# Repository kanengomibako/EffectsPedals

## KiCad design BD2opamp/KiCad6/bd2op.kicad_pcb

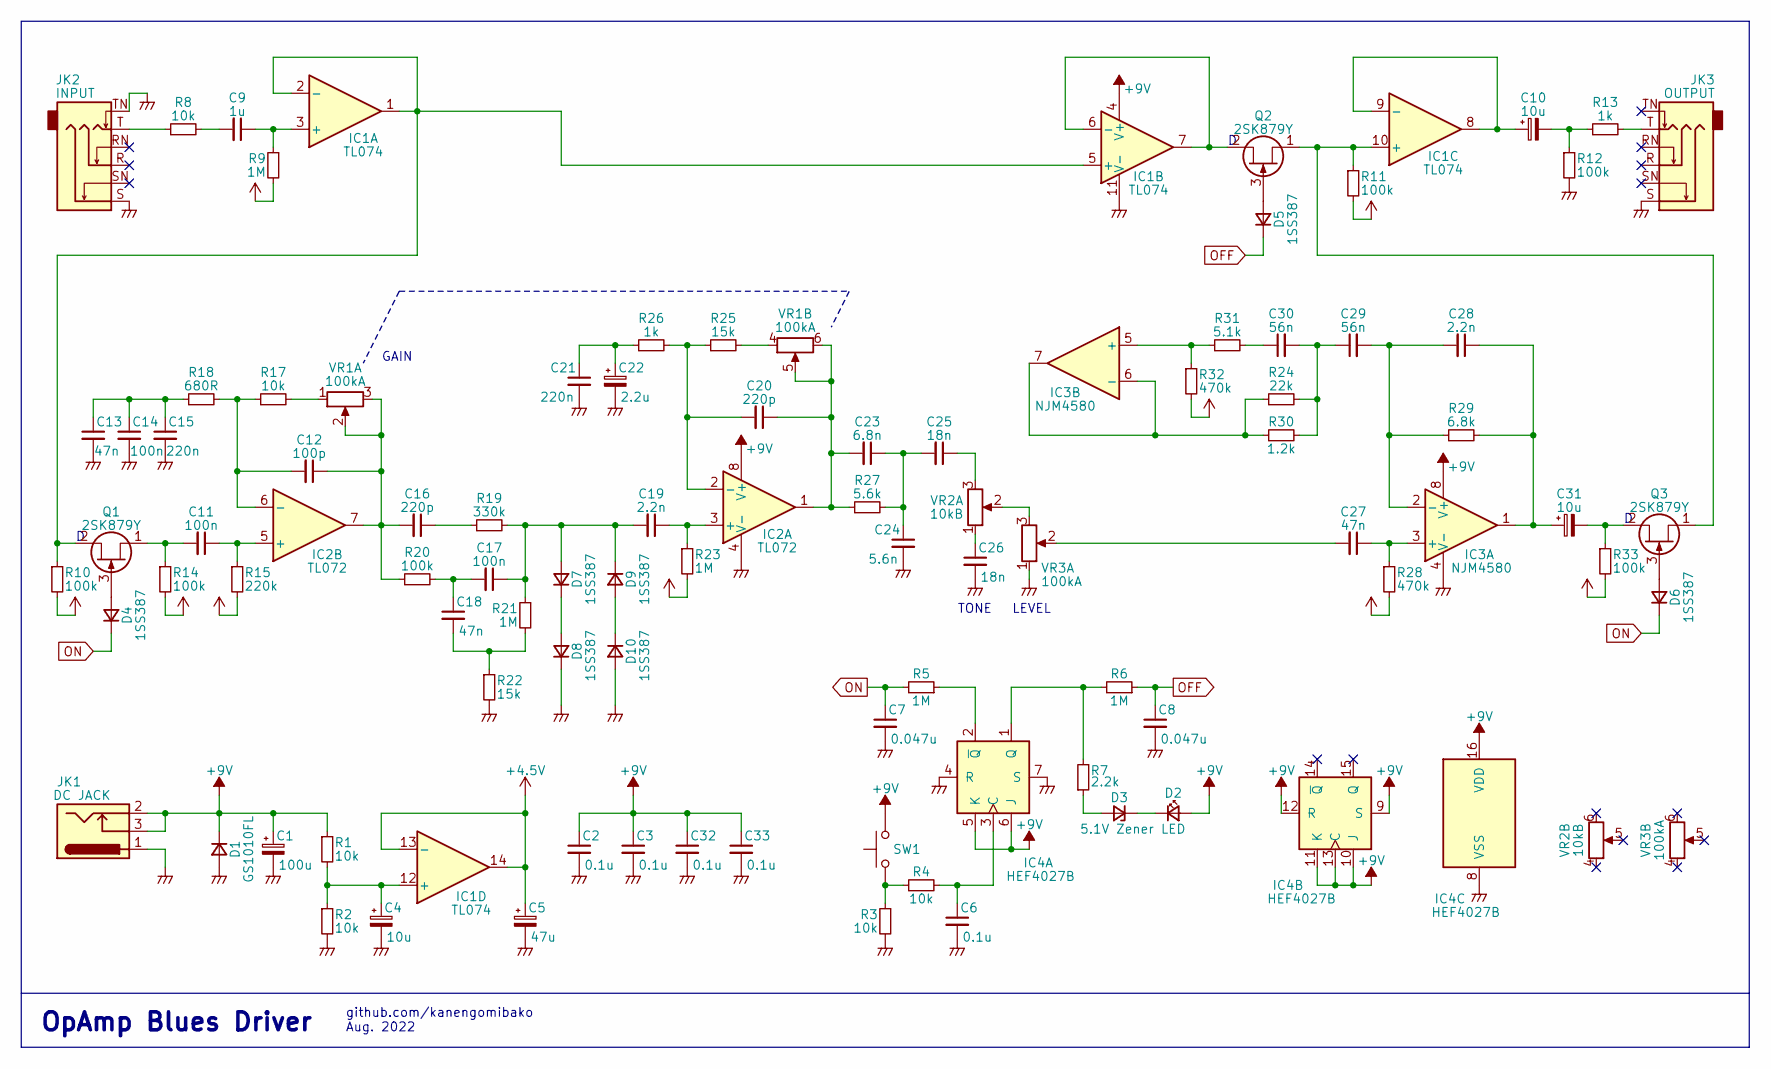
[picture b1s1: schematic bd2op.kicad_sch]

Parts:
C1: 100u; CP_Elec_6.3x5.4_Nichicon
C2, C3, C6, C32, C33: 0.1u; C_0603_1608Metric_Pad1.08x0.95mm_HandSolder
C4, C10, C31: 10u; CP_Elec_4x5.4
C5: 47u; CP_Elec_5x5.4
C7, C8: 0.047u; C_0603_1608Metric_Pad1.08x0.95mm_HandSolder
C9: 1u; C_1206_3216Metric
C11, C17: 100n; C_1206_3216Metric
C12: 100p; C_0603_1608Metric_Pad1.08x0.95mm_HandSolder
C13: 47n; C_1210_3225Metric
C14: 100n; C_1210_3225Metric
C15, C21: 220n; C_1210_3225Metric
C16, C20: 220p; C_0603_1608Metric_Pad1.08x0.95mm_HandSolder
C18, C27: 47n; C_1206_3216Metric
C19, C28: 2.2n; C_0603_1608Metric_Pad1.08x0.95mm_HandSolder
C22: 2.2u; CP_Elec_4x5.4
C23: 6.8n; C_0603_1608Metric_Pad1.08x0.95mm_HandSolder
C24: 5.6n; C_0603_1608Metric_Pad1.08x0.95mm_HandSolder
C25, C26: 18n; C_0805_2012Metric
C29, C30: 56n; C_1206_3216Metric
D1: GS1010FL; my_D_GS1010FL
D2: LED; my_LED_3mm
D3: 5.1V Zener; my_D_SOD-123
D4, D5, D6, D7, D8, D9, D10: 1SS387; D_SOD-523_HandSoldering
IC1: TL074; my_TSSOP-14
IC2: TL072; DIP-8_W7.62mm
IC3: NJM4580; my_SOIC-8_3.9x4.9mm_Pitch1.27mm
IC4: HEF4027B; my_SOIC-16_3.9x9.9mm_Pitch1.27mm
JK1: DC JACK; my_DC_Jack
JK2: INPUT; my_Phone_Jack_Daier
JK3: OUTPUT; my_Phone_Jack_Daier
Q1, Q2, Q3: 2SK879Y; SOT-323_SC-70_Handsoldering
R1, R2, R3, R4, R8, R17: 10k; R_0603_1608Metric_Pad0.98x0.95mm_HandSolder
R5, R6, R9, R21, R23: 1M; R_0603_1608Metric_Pad0.98x0.95mm_HandSolder
R7: 2.2k; R_0603_1608Metric_Pad0.98x0.95mm_HandSolder
R10, R11, R12, R14, R20, R33: 100k; R_0603_1608Metric_Pad0.98x0.95mm_HandSolder
R13, R26: 1k; R_0805_2012Metric
R15: 220k; R_0603_1608Metric_Pad0.98x0.95mm_HandSolder
R18: 680R; R_0805_2012Metric
R19: 330k; R_0603_1608Metric_Pad0.98x0.95mm_HandSolder
R22, R25: 15k; R_0603_1608Metric_Pad0.98x0.95mm_HandSolder
R24: 22k; R_0603_1608Metric_Pad0.98x0.95mm_HandSolder
R27: 5.6k; R_0603_1608Metric_Pad0.98x0.95mm_HandSolder
R28, R32: 470k; R_0603_1608Metric_Pad0.98x0.95mm_HandSolder
R29: 6.8k; R_0603_1608Metric_Pad0.98x0.95mm_HandSolder
R30: 1.2k; R_0603_1608Metric_Pad0.98x0.95mm_HandSolder
R31: 5.1k; R_0603_1608Metric_Pad0.98x0.95mm_HandSolder
SW1: SW_Push; my_SKHCBFA010
VR1, VR3: 100kA; my_pot_slide_20mm_travel
VR2: 10kB; my_pot_slide_20mm_travel

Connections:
+4.5V: C5.1, IC1.13 (-), IC1.14, R9.2, R10.2, R11.2, R14.2, R15.2, R23.2, R28.2, R32.2, R33.2
+9V: C1.1, C2.1, C3.1, C32.1, C33.1, D1.1 (K), D2.2 (A), IC1.4 (V+), IC2.8 (V+), IC3.8 (V+), IC4.5 (K), IC4.6 (J), IC4.9 (S), IC4.10 (J), IC4.11 (K), IC4.12 (R), IC4.13 (C), IC4.16 (VDD), JK1.2, JK1.3, R1.1, SW1.2
GND: C1.2, C2.2, C3.2, C4.2, C5.2, C6.2, C7.2, C8.2, C13.2, C14.2, C15.2, C21.2, C22.2, C24.2, C26.2, C32.2, C33.2, D1.2 (A), D8.1 (K), D10.2 (A), IC1.11 (V-), IC2.4 (V-), IC3.4 (V-), IC4.4 (R), IC4.7 (S), IC4.8 (VSS), JK1.1, JK2.S, JK2.TN, JK3.S, R2.2, R3.2, R12.2, R22.2, VR3.1
unnamed: C4.1, IC1.12 (+), R1.2, R2.1
unnamed: C6.1, IC4.3 (C), R4.2
unnamed: C9.1, IC1.3 (+), R9.1
unnamed: C9.2, R8.2
unnamed: C10.1, IC1.8, IC1.9 (-)
unnamed: C10.2, R12.1, R13.1
unnamed: C11.1, IC2.5 (+), R15.1
unnamed: C11.2, Q1.1 (S), R14.1
unnamed: C12.1, C16.2, IC2.7, R20.1, VR1.2, VR1.3
unnamed: C12.2, IC2.6 (-), R17.1, R18.2
unnamed: C13.1, C14.1, C15.1, R18.1
unnamed: C16.1, R19.1
unnamed: C17.1, C19.2, D7.2 (A), D9.1 (K), R19.2, R21.1
unnamed: C17.2, C18.1, R20.2
unnamed: C18.2, R21.2, R22.1
unnamed: C19.1, IC2.3 (+), R23.1
unnamed: C20.1, C23.2, IC2.1, R27.1, VR1.5, VR1.6
unnamed: C20.2, IC2.2 (-), R25.1, R26.2
unnamed: C21.1, C22.1, R26.1
unnamed: C23.1, C24.1, C25.2, R27.2
unnamed: C25.1, VR2.3
unnamed: C26.1, VR2.1
unnamed: C27.1, IC3.3 (+), R28.1
unnamed: C27.2, VR3.2
unnamed: C28.1, C31.1, IC3.1, R29.2
unnamed: C28.2, C29.2, IC3.2 (-), R29.1
unnamed: C29.1, C30.2, R24.2, R30.2
unnamed: C30.1, R31.2
unnamed: C31.2, Q3.2 (D), R33.1
unnamed: D2.1 (K), D3.1 (K)
unnamed: D3.2 (A), R7.1
unnamed: D4.2 (A), Q1.3 (G)
unnamed: D5.2 (A), Q2.3 (G)
unnamed: D6.2 (A), Q3.3 (G)
unnamed: D7.1 (K), D8.2 (A)
unnamed: D9.2 (A), D10.1 (K)
unnamed: IC1.1, IC1.2 (-), IC1.5 (+), Q1.2 (D), R10.1
unnamed: IC1.6 (-), IC1.7, Q2.2 (D)
unnamed: IC1.10 (+), Q2.1 (S), Q3.1 (S), R11.1
unnamed: IC3.5 (+), R31.1, R32.1
unnamed: IC3.6 (-), IC3.7, R24.1, R30.1
unnamed: IC4.1 (Q), R6.2, R7.2
unnamed: IC4.2 (~Q), R5.1
unnamed: JK2.T, R8.1
unnamed: JK3.T, R13.2
unnamed: R3.1, R4.1, SW1.1
unnamed: R17.2, VR1.1
unnamed: R25.2, VR1.4
unnamed: VR2.2, VR3.3
OFF: C8.1, D5.1 (K), R6.1
ON: C7.1, D4.1 (K), D6.1 (K), R5.2

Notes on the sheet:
OpAmp Blues Driver
GAIN
github.com/kanengomibako Aug. 2022
TONE LEVEL

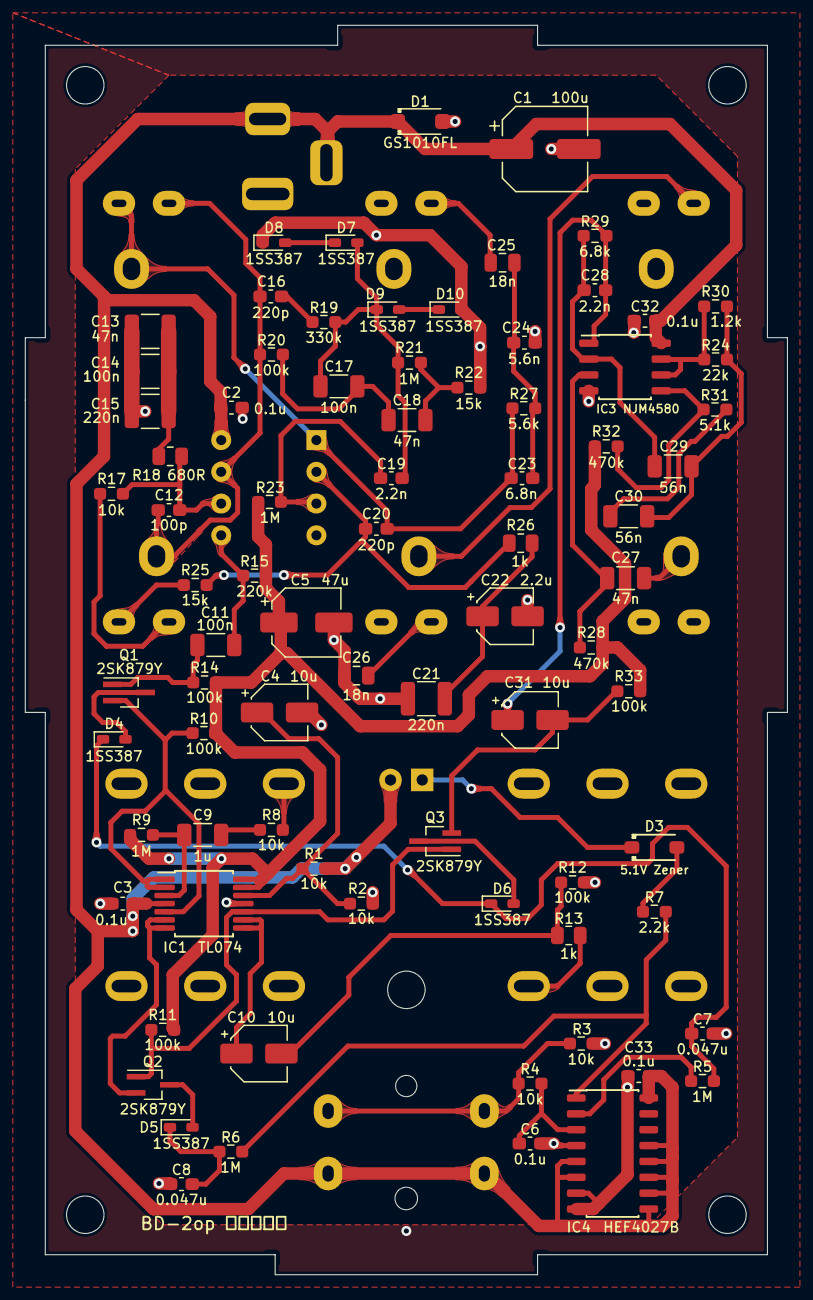
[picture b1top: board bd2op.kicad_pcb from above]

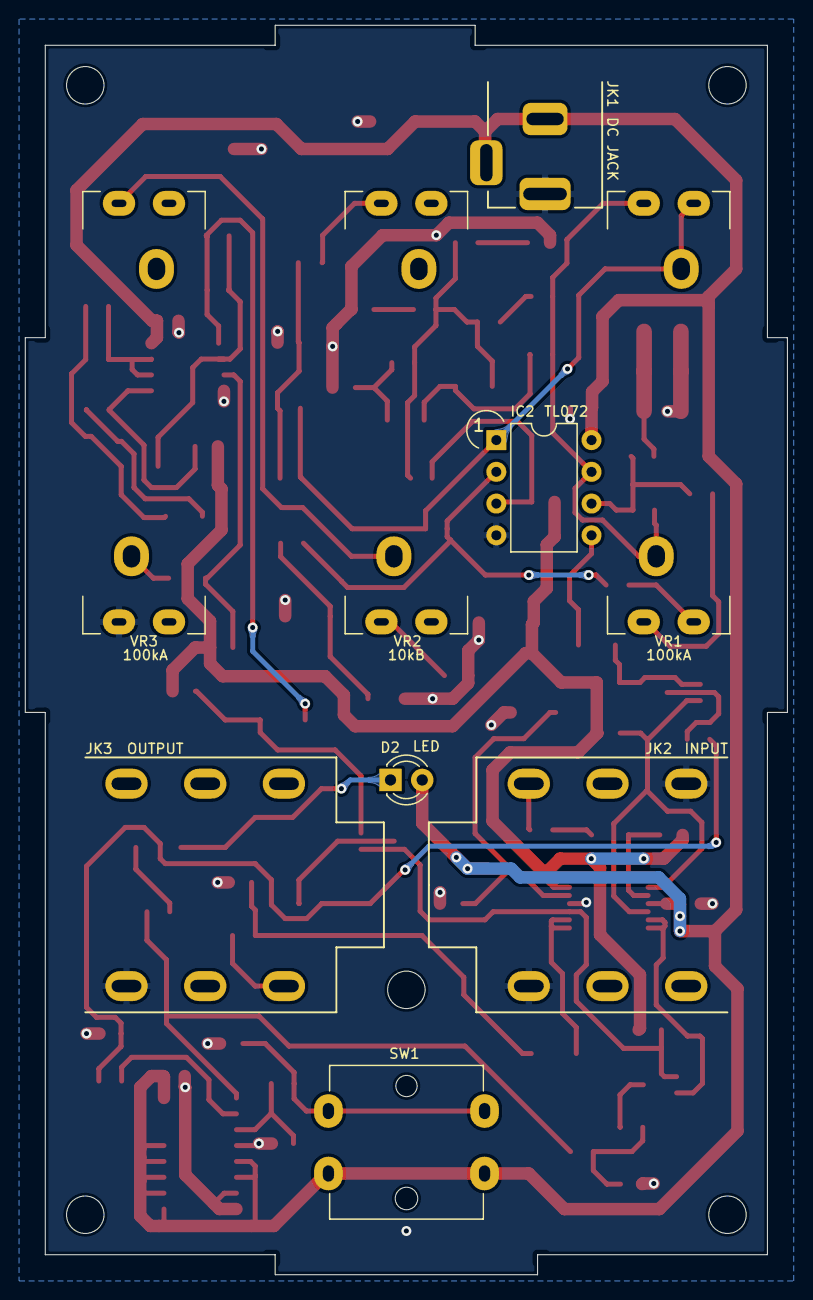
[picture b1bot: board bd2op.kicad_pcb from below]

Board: 2 copper layers, 61.0 x 100.0 mm, 102 parts (9 on the bottom side), 54 nets.

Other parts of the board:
r: h; kado
r#2, r#5, r#7, r#8, r#9, r#11, r#13: h; kado
r#3, r#4, r#6, r#10, r#12: h; Hole_0.4mm

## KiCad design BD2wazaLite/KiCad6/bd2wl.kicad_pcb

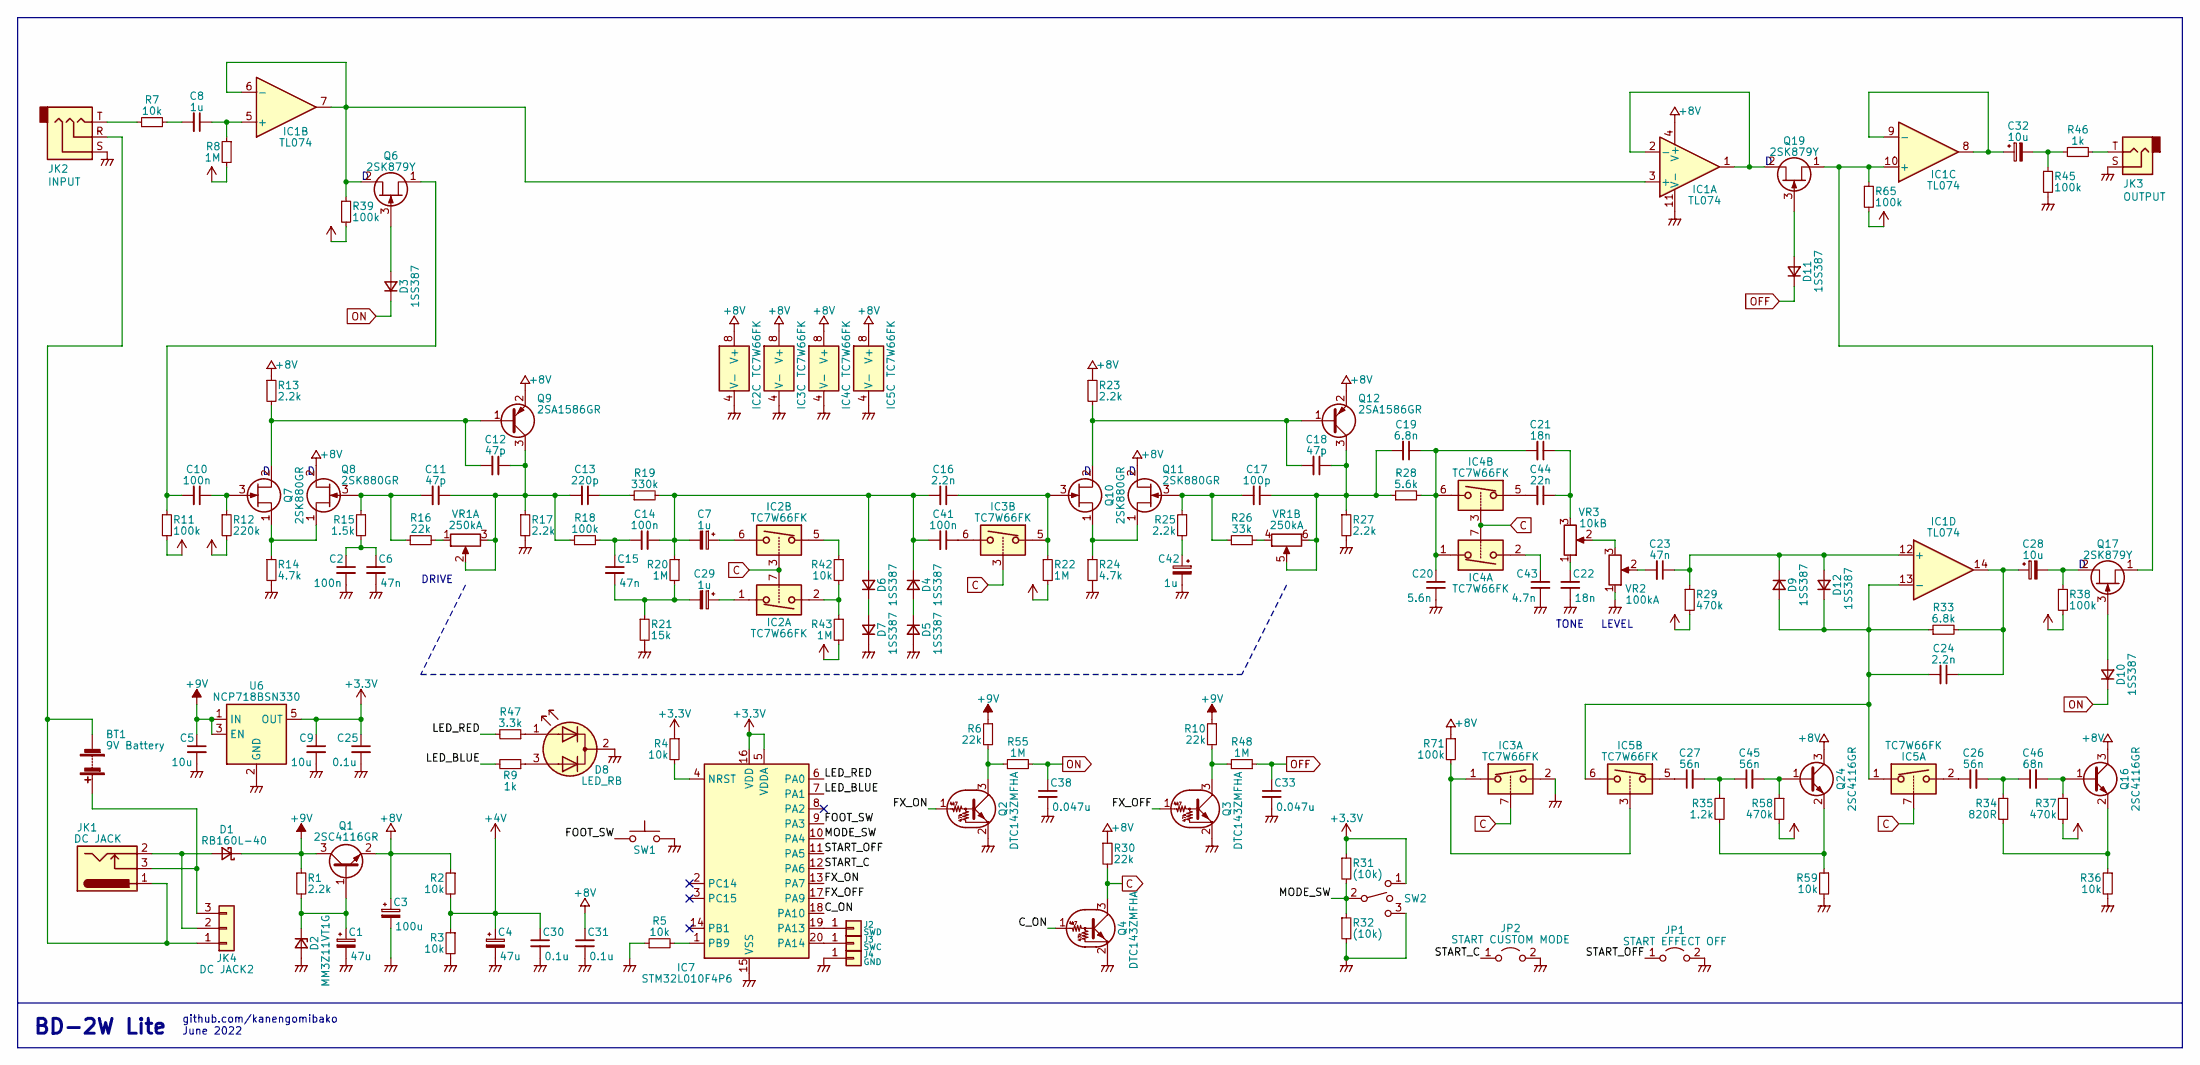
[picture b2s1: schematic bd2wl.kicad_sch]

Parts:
BT1: 9V Battery; PinHeader_1x02_P2.54mm_Vertical
C1, C4: 47u; CP_Elec_5x5.3
C2, C10, C14, C41: 100n; C_1206_3216Metric
C3: 100u; CP_Elec_6.3x5.2
C5, C9: 10u; C_1206_3216Metric
C6, C15, C23: 47n; C_1206_3216Metric
C7, C29, C42: 1u; CP_Elec_4x5.3
C8: 1u; C_1206_3216Metric
C11, C12, C18: 47p; C_0603_1608Metric_Pad1.08x0.95mm_HandSolder
C13: 220p; C_0603_1608Metric_Pad1.08x0.95mm_HandSolder
C16, C24: 2.2n; C_0603_1608Metric_Pad1.08x0.95mm_HandSolder
C17: 100p; C_0603_1608Metric_Pad1.08x0.95mm_HandSolder
C19: 6.8n; C_0603_1608Metric_Pad1.08x0.95mm_HandSolder
C20: 5.6n; C_0603_1608Metric_Pad1.08x0.95mm_HandSolder
C21, C22: 18n; C_0805_2012Metric
C25, C30, C31: 0.1u; C_0603_1608Metric_Pad1.08x0.95mm_HandSolder
C26, C27, C45: 56n; C_1206_3216Metric
C28, C32: 10u; CP_Elec_4x5.3
C33, C38: 0.047u; C_0603_1608Metric_Pad1.08x0.95mm_HandSolder
C43: 4.7n; C_0603_1608Metric_Pad1.08x0.95mm_HandSolder
C44: 22n; C_0805_2012Metric
C46: 68n; C_1206_3216Metric
D1: RB160L-40; D_SMA
D2: MM3Z11VT1G; D_SOD-323_HandSoldering
D3, D4, D5, D6, D7, D9, D10, D11, D12: 1SS387; D_SOD-523_HandSoldering
D8: LED_RB; LED_D3.0mm-3
IC1: TL074; my_TSSOP-14
IC2, IC3, IC4, IC5: TC7W66FK; SSOP8-P-0.50A
IC7: STM32L010F4P6; TSSOP-20_4.4x6.5mm_P0.65mm_HS
J2: SWD; PinHeader_1x01_P2.54mm_Vertical
J3: SWC; PinHeader_1x01_P2.54mm_Vertical
J4: GND; PinHeader_1x01_P2.54mm_Vertical
JK1: DC JACK; my_DC_Jack
JK2: INPUT; PinHeader_1x03_P2.54mm_Vertical
JK3: OUTPUT; PinHeader_1x02_P2.54mm_Vertical
JK4: DC JACK2; PinHeader_1x03_P2.54mm_Vertical
JP1: START EFFECT OFF; my_SolderJumper-THpad-DIPsw
JP2: START CUSTOM MODE; my_SolderJumper-THpad-DIPsw
Q1, Q16, Q24: 2SC4116GR; SOT-323_SC-70_Handsoldering
Q2, Q3, Q4: DTC143ZMFHA; SOT-723_HandSoldering
Q6, Q17, Q19: 2SK879Y; SOT-323_SC-70_Handsoldering
Q7, Q8, Q10, Q11: 2SK880GR; SOT-323_SC-70_Handsoldering
Q9, Q12: 2SA1586GR; SOT-323_SC-70_Handsoldering
R1, R13, R17, R23, R25, R27: 2.2k; R_0603_1608Metric_Pad0.98x0.95mm_HandSolder
R2, R3, R4, R5, R7, R36, R42, R59: 10k; R_0603_1608Metric_Pad0.98x0.95mm_HandSolder
R6, R10, R16, R30: 22k; R_0603_1608Metric_Pad0.98x0.95mm_HandSolder
R8, R20, R22, R43, R48, R55: 1M; R_0603_1608Metric_Pad0.98x0.95mm_HandSolder
R9, R46: 1k; R_0805_2012Metric
R11, R18, R38, R39, R45, R65, R71: 100k; R_0603_1608Metric_Pad0.98x0.95mm_HandSolder
R12: 220k; R_0603_1608Metric_Pad0.98x0.95mm_HandSolder
R14, R24: 4.7k; R_0603_1608Metric_Pad0.98x0.95mm_HandSolder
R15: 1.5k; R_0603_1608Metric_Pad0.98x0.95mm_HandSolder
R19: 330k; R_0603_1608Metric_Pad0.98x0.95mm_HandSolder
R21: 15k; R_0603_1608Metric_Pad0.98x0.95mm_HandSolder
R26: 33k; R_0603_1608Metric_Pad0.98x0.95mm_HandSolder
R28: 5.6k; R_0603_1608Metric_Pad0.98x0.95mm_HandSolder
R29, R37, R58: 470k; R_0603_1608Metric_Pad0.98x0.95mm_HandSolder
R31, R32: (10k); R_0603_1608Metric_Pad0.98x0.95mm_HandSolder
R33: 6.8k; R_0603_1608Metric_Pad0.98x0.95mm_HandSolder
R34: 820R; R_0805_2012Metric
R35: 1.2k; R_0603_1608Metric_Pad0.98x0.95mm_HandSolder
R47: 3.3k; R_0805_2012Metric
SW1: ON/OFF; PinHeader_1x02_P2.54mm_Vertical
SW2: MODE; PinHeader_1x03_P2.54mm_Vertical
U6: NCP718BSN330; SOT-23-5_HandSoldering
VR1: 250kA; PinHeader_2x03_P2.54mm_Vertical
VR2: 100kA; PinHeader_1x03_P2.54mm_Vertical
VR3: 10kB; PinHeader_1x03_P2.54mm_Vertical

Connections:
+3V3: C9.1, C25.1, IC7.5 (VDDA), IC7.16 (VDD), R4.1, R31.1, SW2.1, U6.5 (OUT)
+4V: C4.1, C30.1, R2.2, R3.1, R8.2, R11.2, R12.2, R22.2, R29.2, R37.2, R38.2, R39.2, R43.2, R58.2, R65.2
+8V: C3.1, C31.1, IC1.4 (V+), IC2.8 (V+), IC3.8 (V+), IC4.8 (V+), IC5.8 (V+), Q1.2 (E), Q8.2 (D), Q9.2 (E), Q11.2 (D), Q12.2 (E), Q16.3 (C), Q24.3 (C), R2.1, R13.1, R23.1, R30.1, R71.1
+9V: C5.1, D1.1 (K), Q1.3 (C), R1.1, R6.1, R10.1, U6.1 (IN), U6.3 (EN)
/C_ON: IC7.18 (PA10), Q4.1 (B)
/FOOT_SW: IC7.9 (PA3), SW1.1
/FX_OFF: IC7.17 (PA9), Q3.1 (B)
/FX_ON: IC7.13 (PA7), Q2.1 (B)
/LED_BLUE: IC7.7 (PA1), R9.2
/LED_RED: IC7.6 (PA0), R47.2
/MODE_SW: IC7.10 (PA4), R31.2, R32.1, SW2.2
/START_C: IC7.12 (PA6), JP2.1 (A)
/START_OFF: IC7.11 (PA5), JP1.1 (A)
C: IC2.3, IC2.7, IC3.3, IC3.7, IC4.3, IC4.7, IC5.7, Q4.3 (C), R30.2
GND: C1.2, C2.2, C3.2, C4.2, C5.2, C6.2, C9.2, C20.2, C22.2, C25.2, C30.2, C31.2, C33.2, C38.2, C42.2, C43.2, D2.2 (A), D5.2 (A), D7.1 (K), D8.2 (K), IC1.11 (V-), IC2.4 (V-), IC3.2, IC3.4 (V-), IC4.4 (V-), IC5.4 (V-), IC7.15 (VSS), J4.1, JK2.S, JK3.S, JP1.2 (B), JP2.2 (B), Q2.2 (E), Q3.2 (E), Q4.2 (E), R3.2, R5.1, R14.2, R17.2, R21.2, R24.2, R27.2, R32.2, R36.2, R45.2, R59.2, SW1.2, SW2.3, U6.2 (GND), VR2.1
unnamed: BT1.1 (+), JK1.3, JK4.3
unnamed: BT1.2 (-), JK1.1, JK2.R, JK4.1
unnamed: C1.1, D2.1 (K), Q1.1 (B), R1.2
unnamed: C2.1, C6.1, R15.2
unnamed: C7.1, IC2.6
unnamed: C8.1, IC1.5 (+), R8.1
unnamed: C8.2, R7.2
unnamed: C10.1, Q7.3 (G), R12.1
unnamed: C10.2, Q6.1 (S), R11.1
unnamed: C11.1, C12.1, C13.2, Q9.3 (C), R17.1, R18.1, VR1.2, VR1.3
unnamed: C11.2, Q8.3 (G), R15.1, R16.1
unnamed: C12.2, Q7.2 (D), Q9.1 (B), R13.2
unnamed: C13.1, R19.1
unnamed: C7.2, C14.1, C16.2, C41.2, D4.1 (K), D6.2 (A), R19.2, R20.1
unnamed: C14.2, C15.1, R18.2
unnamed: C15.2, C29.2, R20.2, R21.1
unnamed: C16.1, IC3.5, Q10.3 (G), R22.1
unnamed: C17.1, C18.1, C19.2, Q12.3 (C), R27.1, R28.1, VR1.5, VR1.6
unnamed: C17.2, Q11.3 (G), R25.1, R26.1
unnamed: C18.2, Q10.2 (D), Q12.1 (B), R23.2
unnamed: C19.1, C20.1, C21.2, IC4.1, IC4.6, R28.2
unnamed: C21.1, C44.1, VR3.3
unnamed: C22.1, VR3.1
unnamed: C23.1, D9.1 (K), D12.2 (A), IC1.12 (+), R29.1
unnamed: C23.2, VR2.2
unnamed: C24.1, C28.1, IC1.14, R33.2
unnamed: C24.2, D9.2 (A), D12.1 (K), IC1.13 (-), IC5.1, IC5.6, R33.1
unnamed: C26.1, IC5.2
unnamed: C26.2, C46.1, R34.1
unnamed: C27.1, IC5.5
unnamed: C27.2, C45.1, R35.1
unnamed: C28.2, Q17.2 (D), R38.1
unnamed: C29.1, IC2.1
unnamed: C32.1, IC1.8, IC1.9 (-)
unnamed: C32.2, R45.1, R46.1
unnamed: C41.1, IC3.6
unnamed: C42.1, R25.2
unnamed: C43.1, IC4.2
unnamed: C44.2, IC4.5
unnamed: C45.2, Q24.1 (B), R58.1
unnamed: C46.2, Q16.1 (B), R37.1
unnamed: D1.2 (A), JK1.2, JK4.2
unnamed: D3.2 (A), Q6.3 (G)
unnamed: D4.2 (A), D5.1 (K)
unnamed: D6.1 (K), D7.2 (A)
unnamed: D8.1 (A1), R47.1
unnamed: D8.3 (A2), R9.1
unnamed: D10.2 (A), Q17.3 (G)
unnamed: D11.2 (A), Q19.3 (G)
unnamed: IC1.1, IC1.2 (-), Q19.2 (D)
unnamed: IC1.3 (+), IC1.6 (-), IC1.7, Q6.2 (D), R39.1
unnamed: IC1.10 (+), Q17.1 (S), Q19.1 (S), R65.1
unnamed: IC2.2, R42.2, R43.1
unnamed: IC2.5, R42.1
unnamed: IC3.1, IC5.3, R71.2
unnamed: IC7.1 (PB9), R5.2
unnamed: IC7.4 (NRST), R4.2
unnamed: IC7.19 (PA13), J2.1
unnamed: IC7.20 (PA14), J3.1
unnamed: JK2.T, R7.1
unnamed: JK3.T, R46.2
unnamed: Q2.3 (C), R6.2, R55.1
unnamed: Q3.3 (C), R10.2, R48.2
unnamed: Q7.1 (S), Q8.1 (S), R14.1
unnamed: Q10.1 (S), Q11.1 (S), R24.1
unnamed: Q16.2 (E), R34.2, R36.1
unnamed: Q24.2 (E), R35.2, R59.1
unnamed: R16.2, VR1.1
unnamed: R26.2, VR1.4
unnamed: VR2.3, VR3.2
OFF: C33.1, D11.1 (K), R48.1
ON: C38.1, D3.1 (K), D10.1 (K), R55.2

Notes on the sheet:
BD-2W Lite
DRIVE
github.com/kanengomibako June 2022
TONE LEVEL

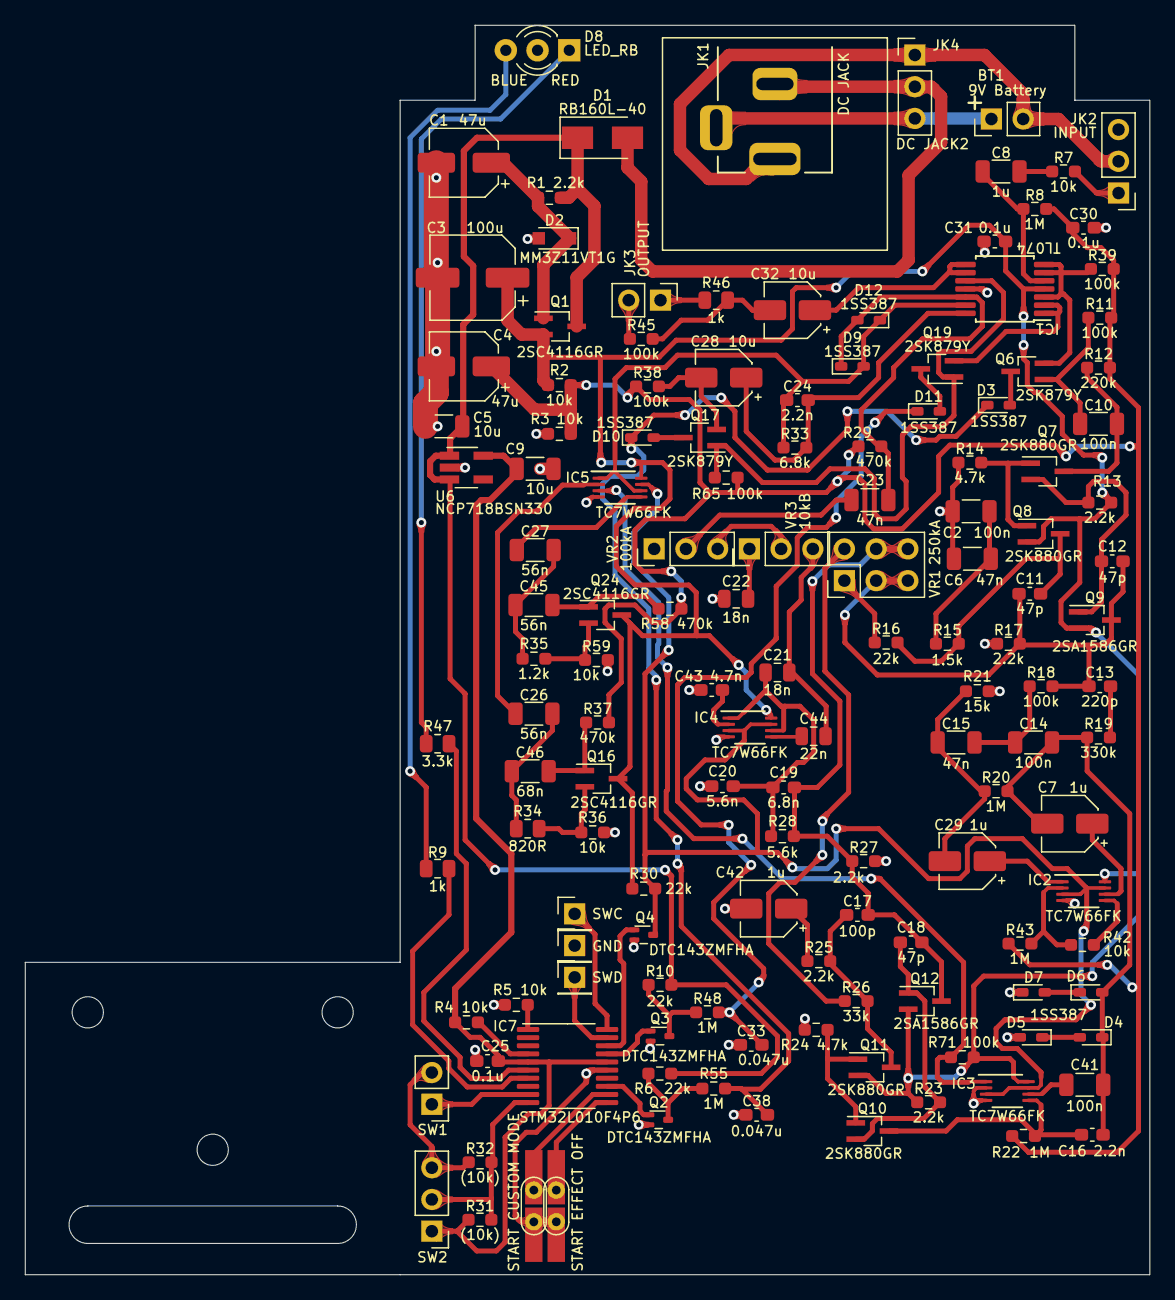
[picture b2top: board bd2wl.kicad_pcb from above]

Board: 2 copper layers, 90.0 x 100.0 mm, 144 parts (0 on the bottom side), 87 nets.

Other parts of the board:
*: a; my_Hole_1.0mm
*#2, *#3, *#4, *#5: a; my_Hole_1.0mm
